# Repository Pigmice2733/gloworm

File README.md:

# Gloworm

A Raspberry Pi vision tracking module for FRC.

* Powered directly off the PDP (built-in Raspberry Pi PSU)
* Cheap, utilizing off the shelf parts and a 3D printed case (~$120 including RPi 4, camera, PCB, fasteners)
* Fully dimmable ~500 lumen output (6x Cree XP-E2 Green LEDs)
* Compact design (100mm x 74mm x 25mm)

<br />This work is licensed under a <a rel="license" href="http://creativecommons.org/licenses/by-nc-sa/4.0/">Creative Commons Attribution-NonCommercial-ShareAlike 4.0 International License</a>.

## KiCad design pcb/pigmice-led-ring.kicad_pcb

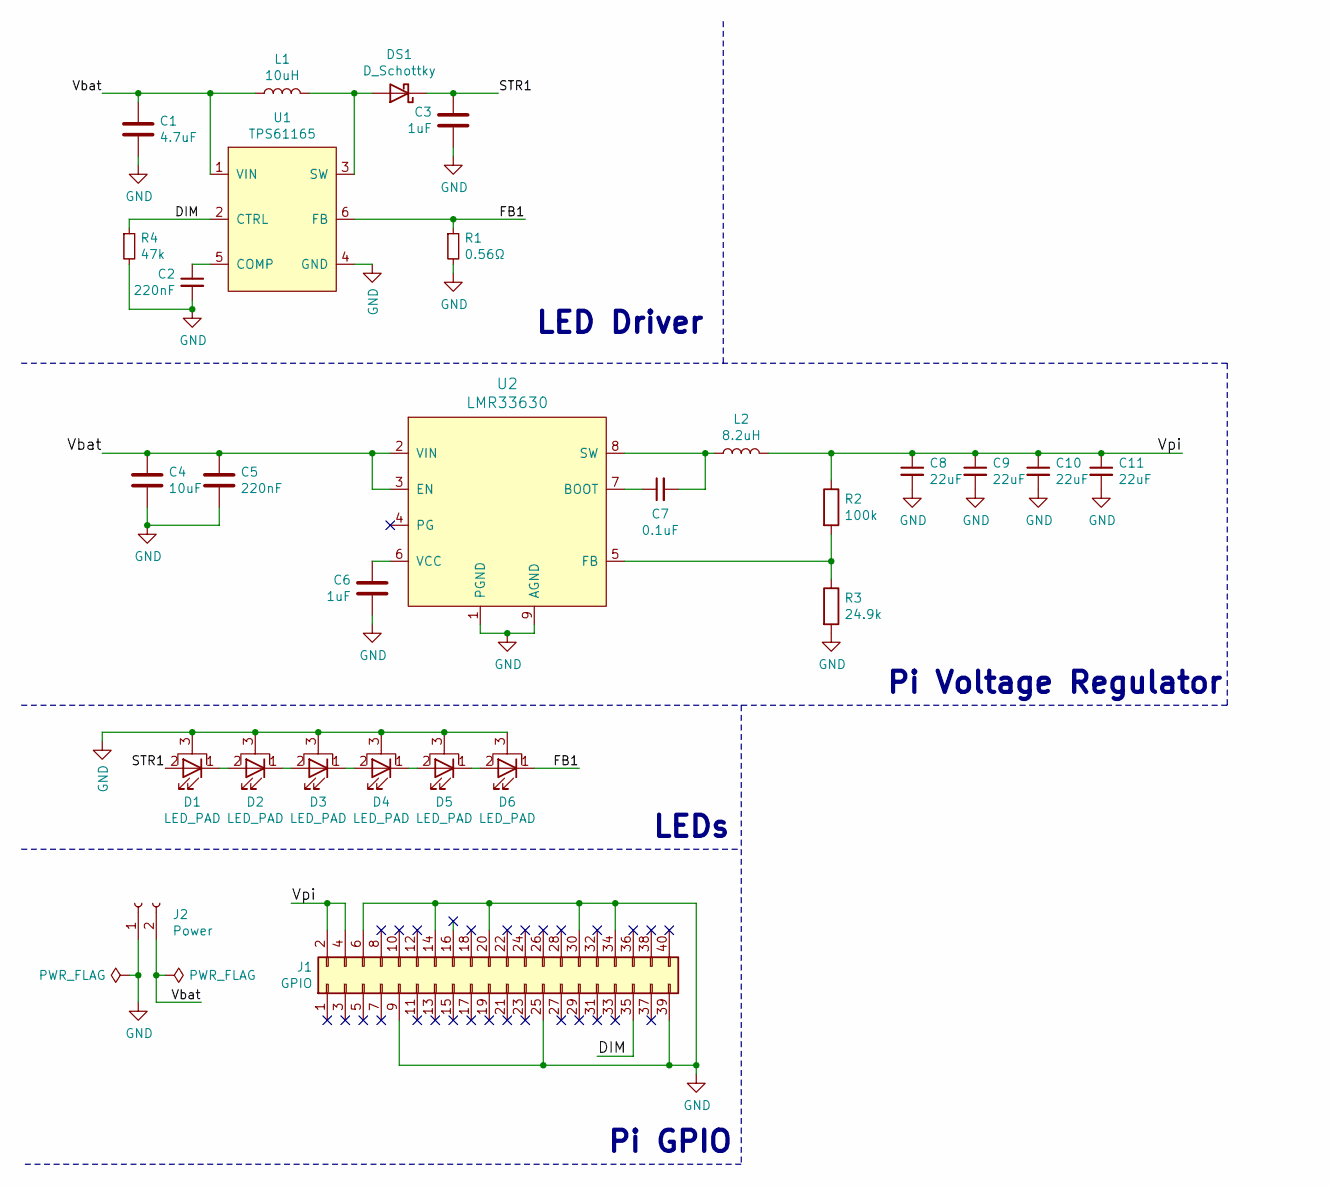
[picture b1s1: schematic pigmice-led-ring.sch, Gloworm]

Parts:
C1: 4.7uF; C_0805_2012Metric; Digikey 445-172480-1-ND
C2: 220nF; C_0805_2012Metric; Digikey 490-13311-1-ND
C3, C6: 1uF; C_0603_1608Metric; Digikey 1276-6524-1-ND
C4: 10uF; C_1210_3225Metric; Digikey 1276-3388-1-ND
C5: 220nF; C_0603_1608Metric; Digikey 490-5402-1-ND
C7: 0.1uF; C_0603_1608Metric; Digikey 490-16327-1-ND
C8, C9, C10, C11: 22uF; C_1210_3225Metric; Digikey 490-14682-1-ND
D1, D2, D3, D4, D5, D6: LED_PAD; LED_Cree-XP; Digikey XPEBGR-L1-0000-00D01CT-ND
DS1: D_Schottky; D_SOD-123; Digikey MBR0540CT-ND
J1: GPIO; PinSocket_2x20_P2.54mm_Vertical; Digikey A26468-ND
J2: Power; TE_282837-2; Digikey A113320-ND
L1: 10uH; IND_#A915AY-100M=P3; Digikey 490-16513-1-ND
L2: 8.2uH; L_Vishay_IHLP-2525; Digikey 541-1012-1-ND
R1: 0.56Ω; R_0805_2012Metric; Digikey P19302CT-ND
R2: 100k; R_0603_1608Metric; Digikey P100KDBCT-ND
R3: 24.9k; R_0603_1608Metric; Digikey P24.9KDBCT-ND
R4: 47k; R_0805_2012Metric; Digikey 311-47KARCT-ND
U1: TPS61165; SOT-23-6; Digikey 296-27597-1-ND
U2: LMR33630; Texas_HSOP-8-1EP_3.9x4.9mm_P1.27mm_ThermalVias; Digikey 296-49763-1-ND

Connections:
/DIM: J1.35, R4.1, U1.2 (CTRL)
/FB1: D6.1 (K), R1.1, U1.6 (FB)
/STR1: C3.1, D1.2 (A), DS1.1 (K)
/Vbat: C1.1, C4.1, C5.1, J2.2, L1.1, U1.1 (VIN), U2.2 (VIN), U2.3 (EN)
/Vpi: C8.1, C9.1, C10.1, C11.1, J1.2, J1.4, L2.2, R2.1
GND: C1.2, C2.2, C3.2, C4.2, C5.2, C6.2, C8.2, C9.2, C10.2, C11.2, D1.3 (PAD), D2.3 (PAD), D3.3 (PAD), D4.3 (PAD), D5.3 (PAD), D6.3 (PAD), J1.6, J1.9, J1.14, J1.20, J1.25, J1.30, J1.34, J1.39, J2.1, R1.2, R3.2, R4.2, U1.4 (GND), U2.1 (PGND), U2.9 (AGND)
unnamed: C2.1, U1.5 (COMP)
unnamed: C6.1, U2.6 (VCC)
unnamed: C7.1, U2.7 (BOOT)
unnamed: C7.2, L2.1, U2.8 (SW)
unnamed: D1.1 (K), D2.2 (A)
unnamed: D2.1 (K), D3.2 (A)
unnamed: D3.1 (K), D4.2 (A)
unnamed: D4.1 (K), D5.2 (A)
unnamed: D5.1 (K), D6.2 (A)
unnamed: DS1.2 (A), L1.2, U1.3 (SW)
unnamed: R2.2, R3.1, U2.5 (FB)

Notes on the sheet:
LED Driver
Pi Voltage Regulator
LEDs
Pi GPIO

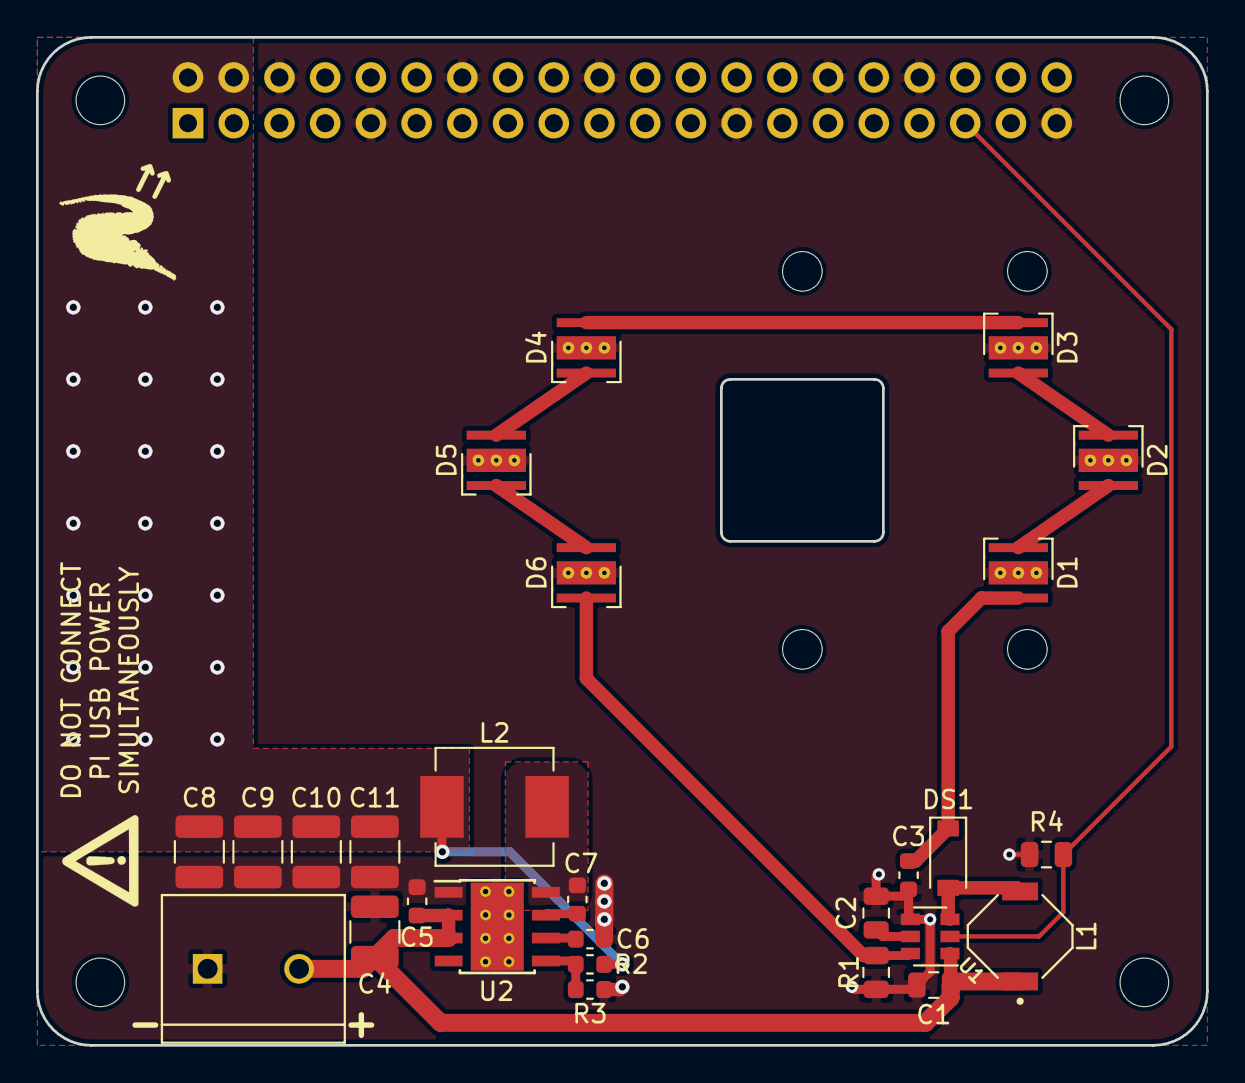
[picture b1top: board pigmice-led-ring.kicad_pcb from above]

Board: 2 copper layers, 65.0 x 56.0 mm, 28 parts (1 on the bottom side), 17 nets.

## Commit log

2020-03-03 Add KiCAD PCB files
2020-03-03 Add case CAD files
2020-03-03 Add initial README and license
2020-03-04 Cleanup PCB
    - Order 5v output capacitors
    - Don't show J1 and J2 footprints
    - Add OSHW logo to the back
2020-06-09 Better .gitignore for PCB
2020-06-09 Clean up libraries, schematic, PCB
    * Consolidate footprint and symbol libraries
    * Fix Cree XP E-2 thermal vias
    * GND planes on both sides
    * Vpi copper fill on both sides, connected with vias
    * No Vbat copper fill, replaced with 1mm trace
    * Fix all DRC and ERC errors
2020-06-09 Add DIM pull-down, fixup BOM, zone tolerances
